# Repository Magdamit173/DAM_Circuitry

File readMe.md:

"DAM Circuitry" 
"Routing Stage"

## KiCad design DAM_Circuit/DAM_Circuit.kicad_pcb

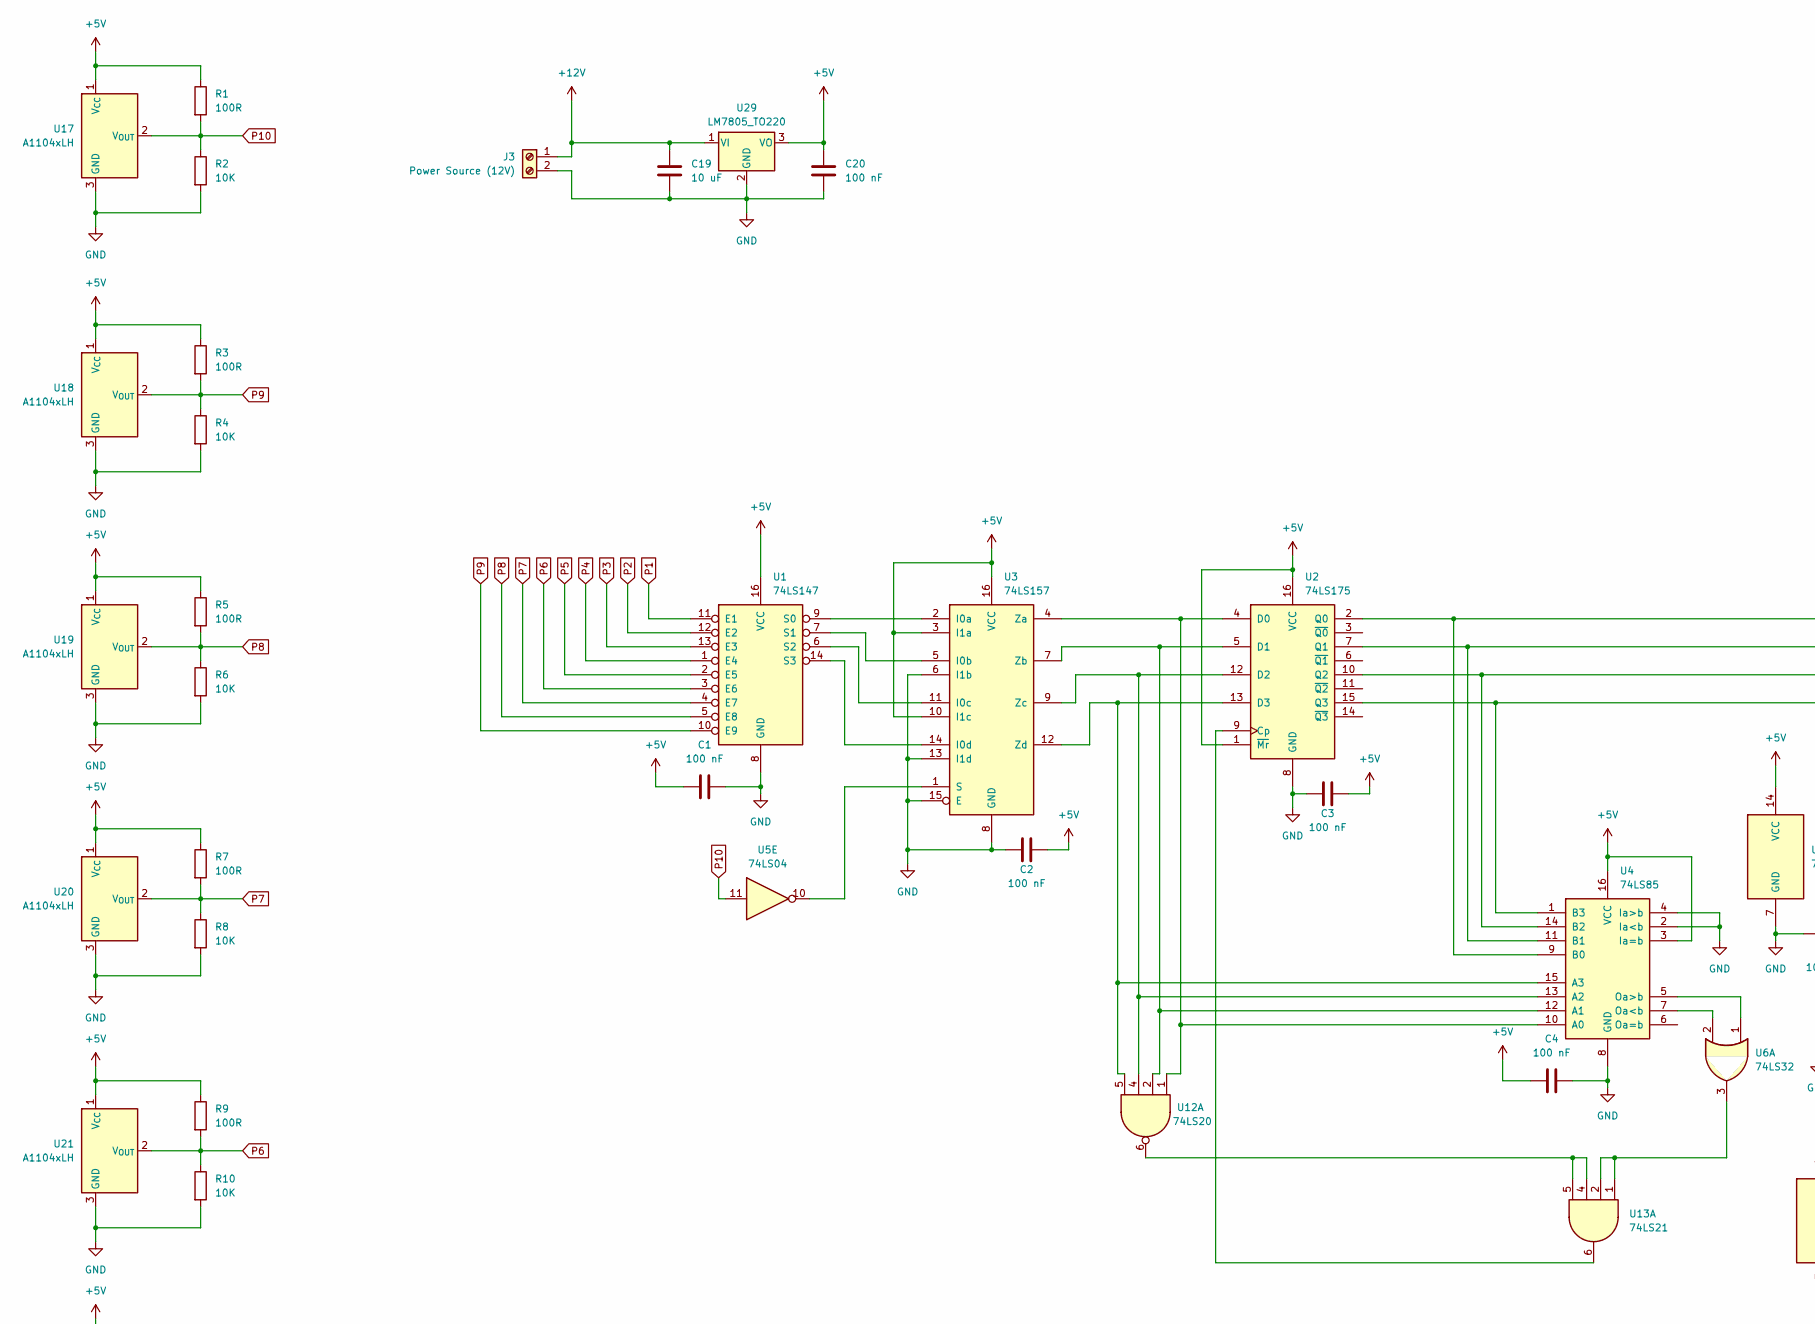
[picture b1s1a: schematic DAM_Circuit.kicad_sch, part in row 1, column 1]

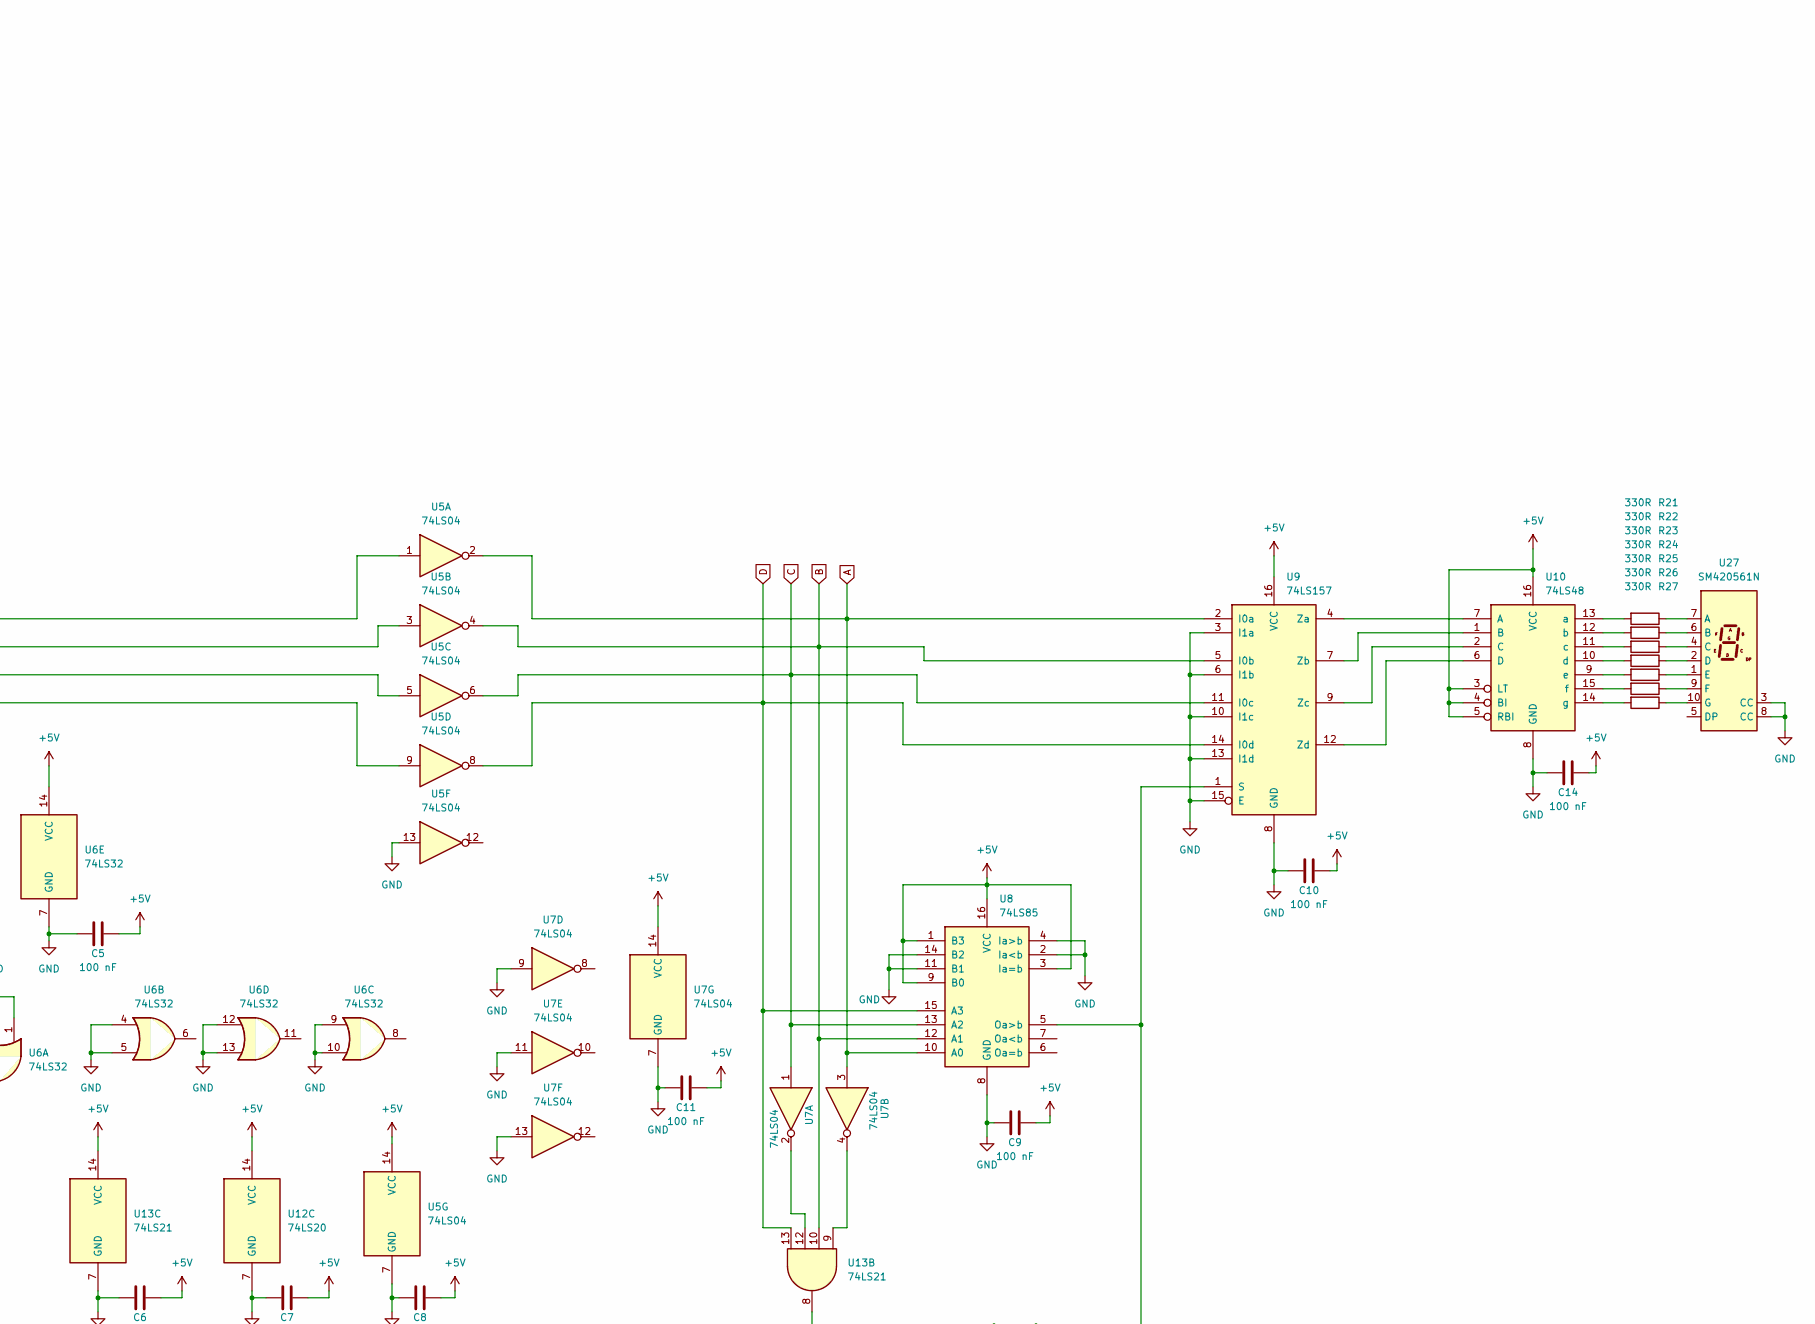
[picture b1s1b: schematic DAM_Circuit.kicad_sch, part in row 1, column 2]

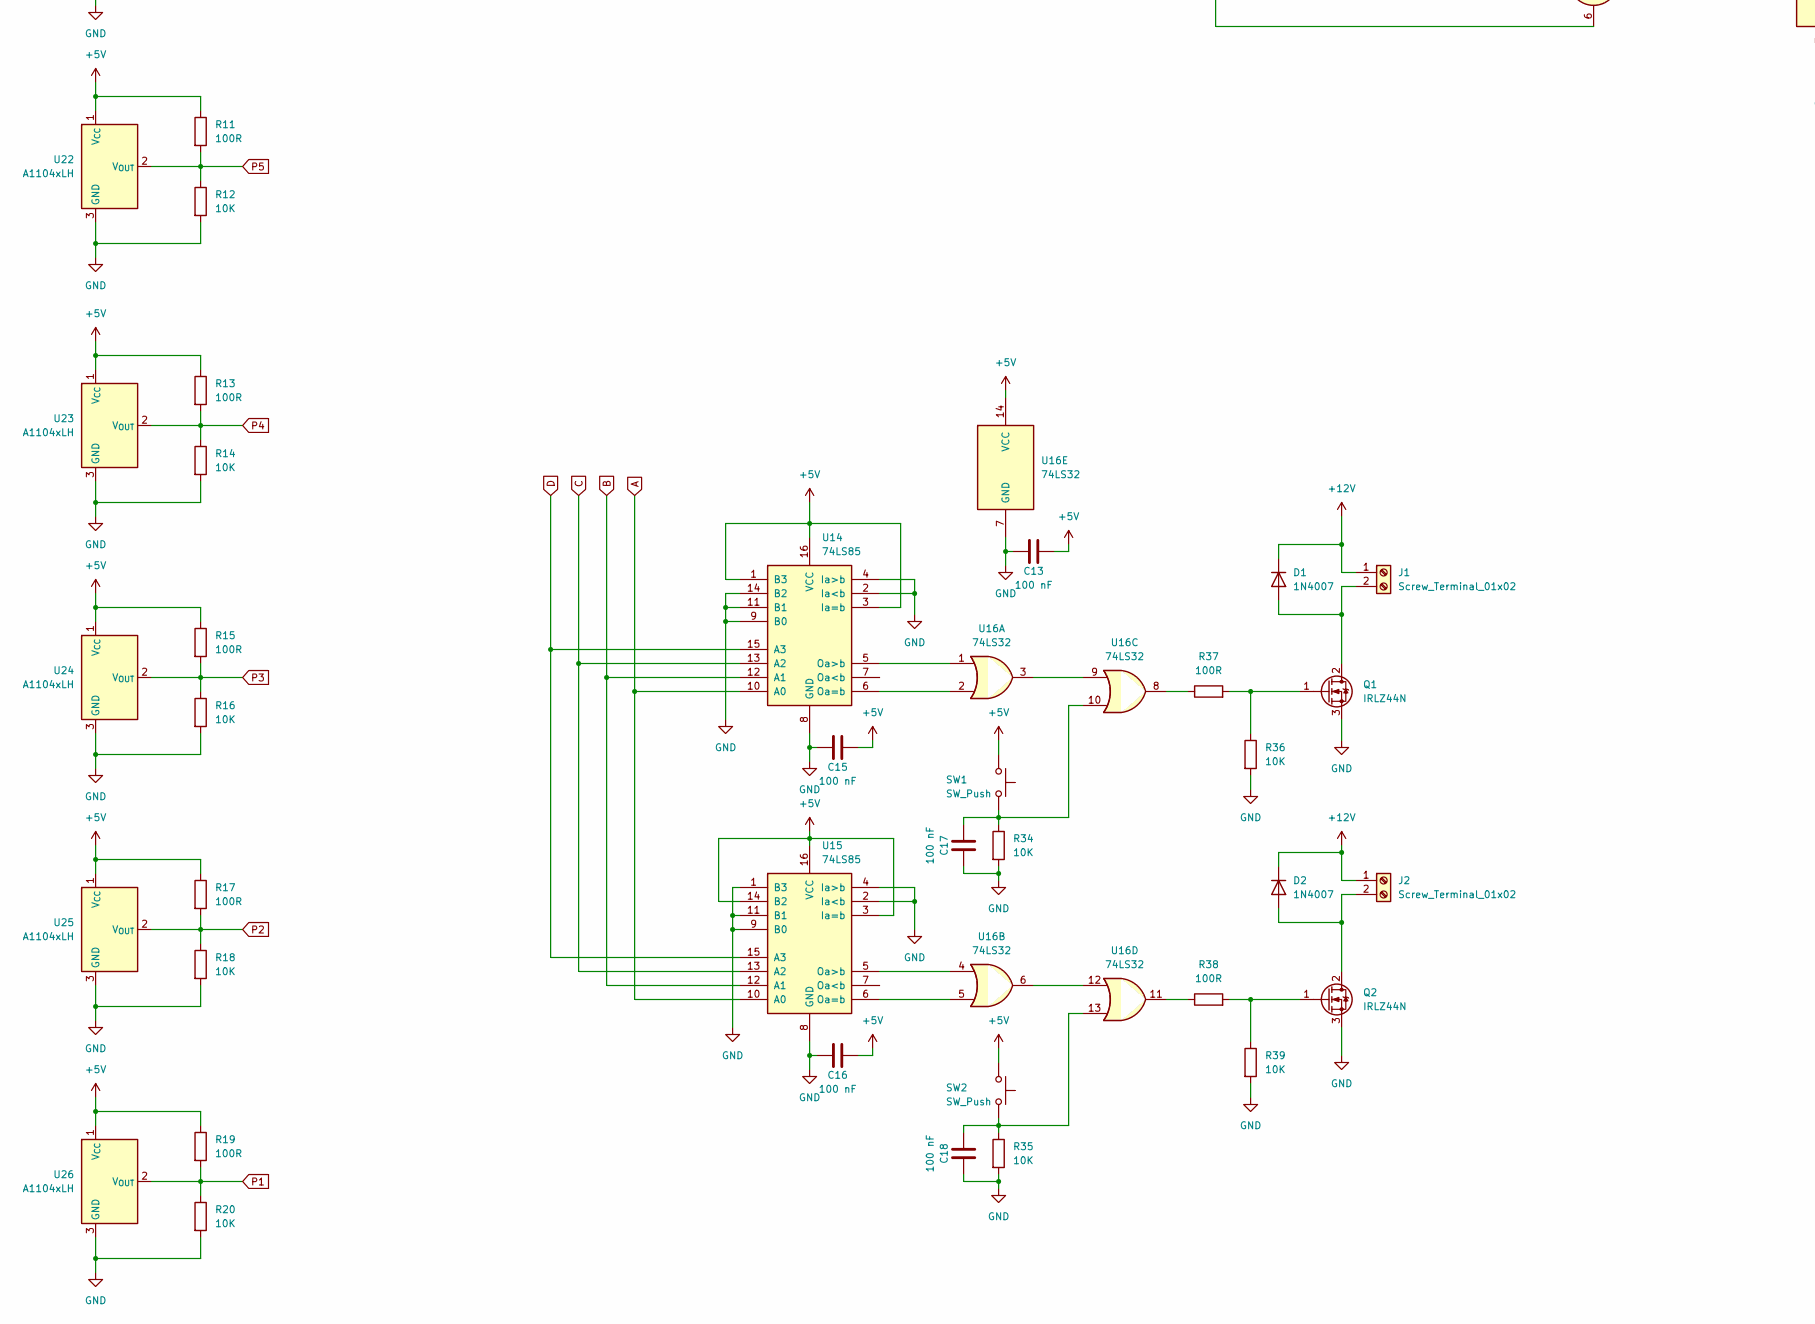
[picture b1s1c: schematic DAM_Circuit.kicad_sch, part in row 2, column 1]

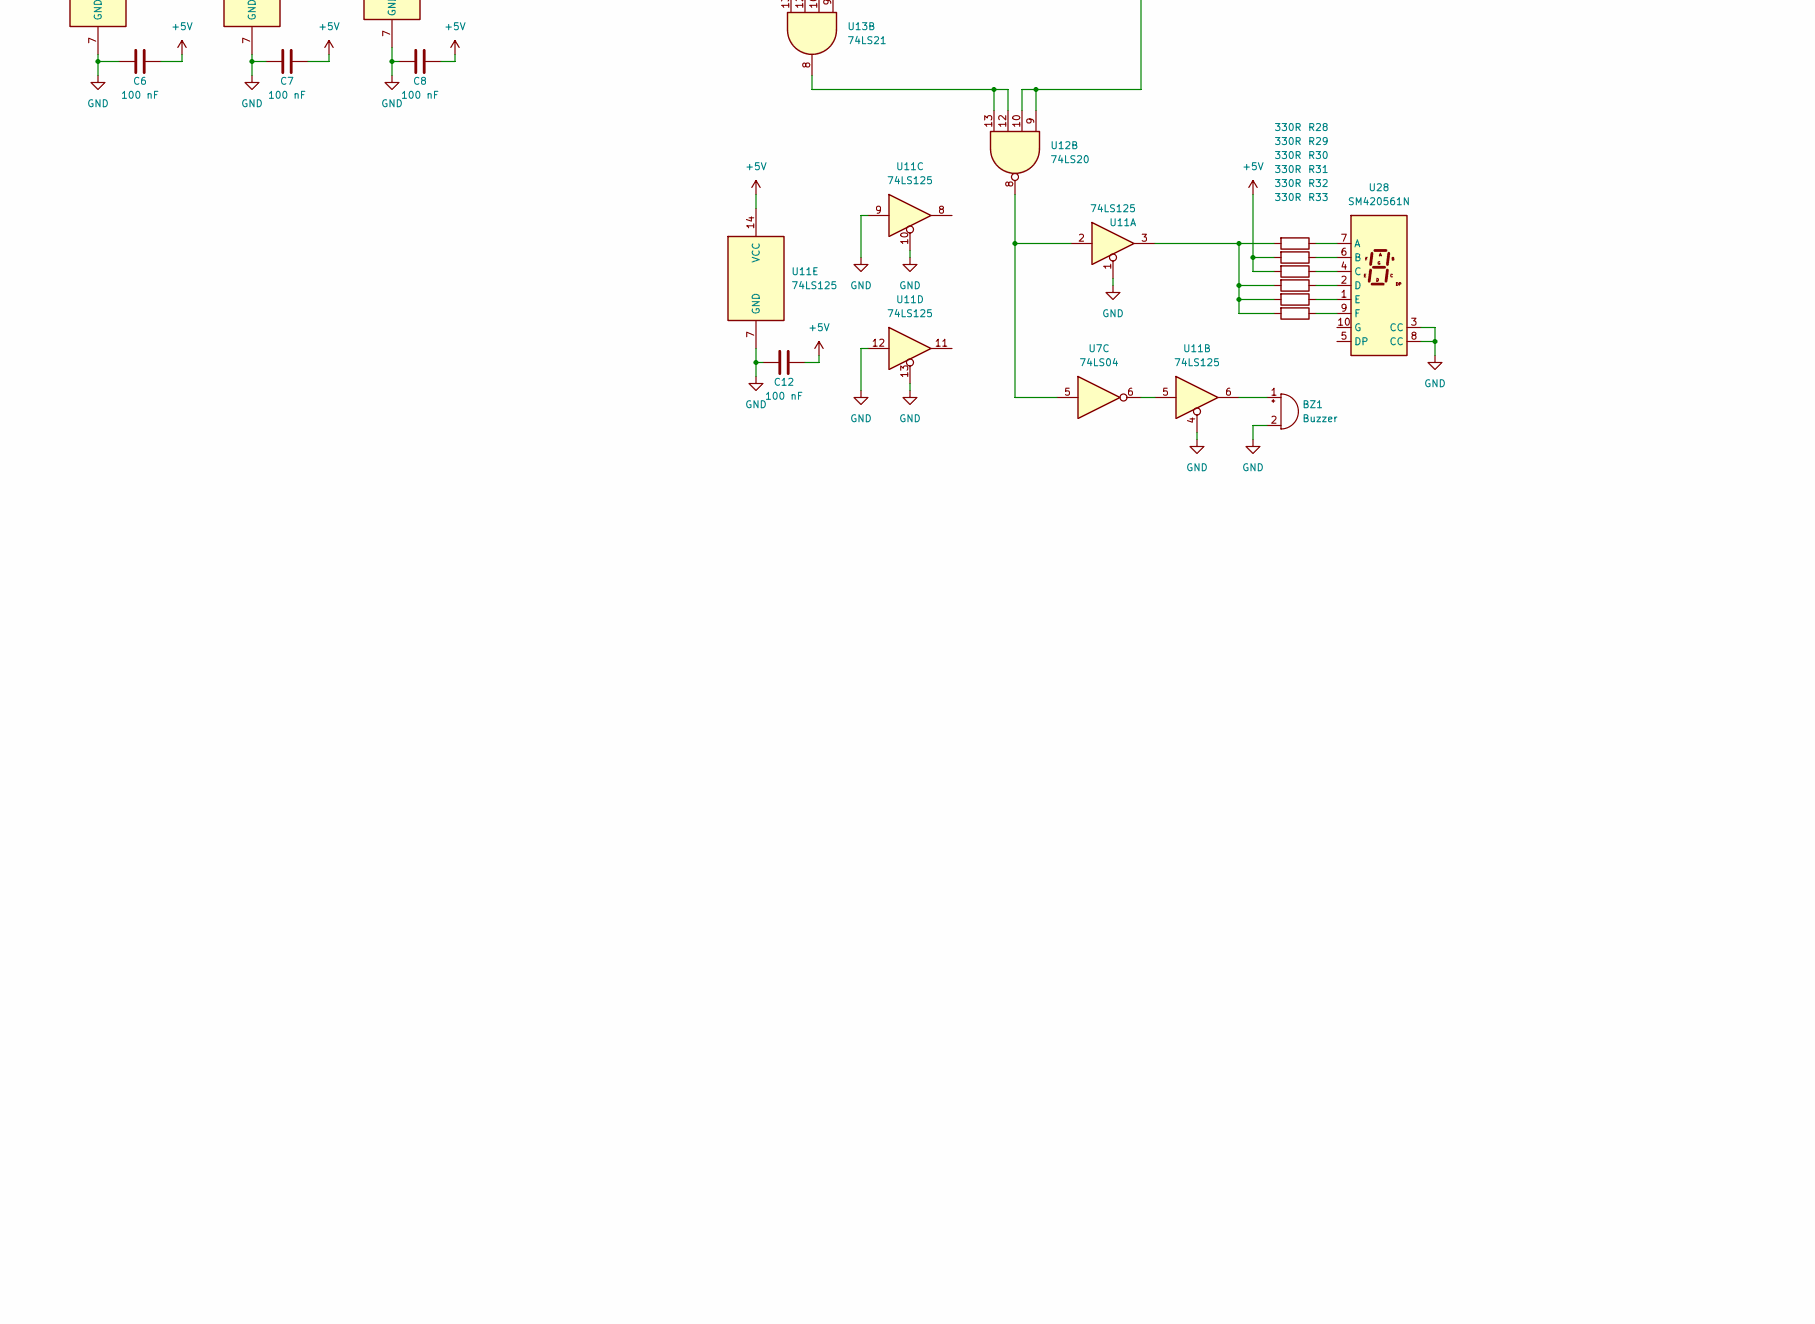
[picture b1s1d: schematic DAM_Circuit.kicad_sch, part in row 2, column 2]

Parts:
BZ1: Buzzer; TerminalBlock_Phoenix_MKDS-1,5-2_1x02_P5.00mm_Horizontal
C1, C2, C3, C4, C5, C6, C7, C8, C9, C10, C11, C12, C13, C14, C15, C16, C17, C18, C20: 100 nF; C_Disc_D5.0mm_W2.5mm_P5.00mm
C19: 10 uF; C_Disc_D5.0mm_W2.5mm_P5.00mm
D1, D2: 1N4007; D_DO-41_SOD81_P10.16mm_Horizontal
J1, J2: Screw_Terminal_01x02; TerminalBlock_Phoenix_MKDS-1,5-2_1x02_P5.00mm_Horizontal
J3: Power Source (12V); TerminalBlock_Phoenix_MKDS-1,5-2_1x02_P5.00mm_Horizontal
Q1, Q2: IRLZ44N; TO-220-3_Vertical
R1, R3, R5, R7, R9, R11, R13, R15, R17, R19, R37, R38: 100R; R_Axial_DIN0207_L6.3mm_D2.5mm_P10.16mm_Horizontal
R2, R4, R6, R8, R10, R12, R14, R16, R18, R20, R34, R35, R36, R39: 10K; R_Axial_DIN0207_L6.3mm_D2.5mm_P10.16mm_Horizontal
R21, R22, R23, R24, R25, R26, R27, R28, R29, R30, R31, R32, R33: 330R; R_Axial_DIN0207_L6.3mm_D2.5mm_P10.16mm_Horizontal
SW1, SW2: SW_Push; SW_PUSH_6mm_H5mm
U1: 74LS147; DIP-16_W7.62mm
U2: 74LS175; DIP-16_W7.62mm
U3, U9: 74LS157; DIP-16_W7.62mm
U4, U8, U14, U15: 74LS85; DIP-16_W7.62mm
U5, U7: 74LS04; DIP-14_W7.62mm
U6, U16: 74LS32; DIP-14_W7.62mm
U10: 74LS48; DIP-16_W7.62mm
U11: 74LS125; DIP-14_W7.62mm
U12: 74LS20; DIP-14_W7.62mm
U13: 74LS21; DIP-14_W7.62mm
U17, U18, U19, U20, U21, U22, U23, U24, U25, U26: A1104xLH; PinHeader_1x03_P2.54mm_Vertical
U27, U28: SM420561N; 7SegmentLED_LTS6760_LTS6780
U29: LM7805_TO220; TO-220-3_Vertical

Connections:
+5V: C1.1, C2.2, C3.2, C4.1, C5.2, C6.2, C7.2, C8.2, C9.2, C10.2, C11.2, C12.2, C13.2, C14.2, C15.2, C16.2, C20.2, R1.1, R3.1, R5.1, R7.1, R9.1, R11.1, R13.1, R15.1, R17.1, R19.1, R29.2, R30.2, SW1.1, SW2.1, U1.16 (VCC), U2.1 (~Mr), U2.16 (VCC), U3.3 (I1a), U3.10 (I1c), U3.16 (VCC), U4.3 (Ia=b), U4.16 (VCC), U5.14 (VCC), U6.14 (VCC), U7.14 (VCC), U8.1 (B3), U8.3 (Ia=b), U8.9 (B0), U8.16 (VCC), U9.16 (VCC), U10.3 (LT), U10.4 (BI), U10.5 (RBI), U10.16 (VCC), U11.14 (VCC), U12.14 (VCC), U13.14 (VCC), U14.1 (B3), U14.3 (Ia=b), U14.16 (VCC), U15.3 (Ia=b), U15.14 (B2), U15.16 (VCC), U16.14 (VCC), U17.1 (V_{CC}), U18.1 (V_{CC}), U19.1 (V_{CC}), U20.1 (V_{CC}), U21.1 (V_{CC}), U22.1 (V_{CC}), U23.1 (V_{CC}), U24.1 (V_{CC}), U25.1 (V_{CC}), U26.1 (V_{CC}), U29.3 (VO)
+12V: C19.2, D1.1 (K), D2.1 (K), J1.1, J2.1, J3.1, U29.1 (VI)
A: U5.2, U7.3, U8.10 (A0), U9.2 (I0a), U14.10 (A0), U15.10 (A0)
B: U5.4, U8.12 (A1), U9.5 (I0b), U13.10, U14.12 (A1), U15.12 (A1)
C: U5.6, U7.1, U8.13 (A2), U9.11 (I0c), U14.13 (A2), U15.13 (A2)
D: U5.8, U8.15 (A3), U9.14 (I0d), U13.13, U14.15 (A3), U15.15 (A3)
GND: BZ1.2 (-), C1.2, C2.1, C3.1, C4.2, C5.1, C6.1, C7.1, C8.1, C9.1, C10.1, C11.1, C12.1, C13.1, C14.1, C15.1, C16.1, C17.2, C18.2, C19.1, C20.1, J3.2, Q1.3 (S), Q2.3 (S), R2.2, R4.2, R6.2, R8.2, R10.2, R12.2, R14.2, R16.2, R18.2, R20.2, R34.2, R35.2, R36.2, R39.2, U1.8 (GND), U2.8 (GND), U3.6 (I1b), U3.8 (GND), U3.13 (I1d), U3.15 (E), U4.2 (Ia<b), U4.4 (Ia>b), U4.8 (GND), U5.7 (GND), U5.13, U6.4, U6.5, U6.7 (GND), U6.9, U6.10, U6.12, U6.13, U7.7 (GND), U7.9, U7.11, U7.13, U8.2 (Ia<b), U8.4 (Ia>b), U8.8 (GND), U8.11 (B1), U8.14 (B2), U9.3 (I1a), U9.6 (I1b), U9.8 (GND), U9.10 (I1c), U9.13 (I1d), U9.15 (E), U10.8 (GND), U11.1, U11.4, U11.7 (GND), U11.9, U11.10, U11.12, U11.13, U12.7 (GND), U13.7 (GND), U14.2 (Ia<b), U14.4 (Ia>b), U14.8 (GND), U14.9 (B0), U14.11 (B1), U14.14 (B2), U15.1 (B3), U15.2 (Ia<b), U15.4 (Ia>b), U15.8 (GND), U15.9 (B0), U15.11 (B1), U16.7 (GND), U17.3 (GND), U18.3 (GND), U19.3 (GND), U20.3 (GND), U21.3 (GND), U22.3 (GND), U23.3 (GND), U24.3 (GND), U25.3 (GND), U26.3 (GND), U27.3 (CC), U27.8 (CC), U28.3 (CC), U28.8 (CC), U29.2 (GND)
unnamed: BZ1.1 (+), U11.6
unnamed: C17.1, R34.1, SW1.2, U16.10
unnamed: C18.1, R35.1, SW2.2, U16.13
unnamed: D1.2 (A), J1.2, Q1.2 (D)
unnamed: D2.2 (A), J2.2, Q2.2 (D)
unnamed: Q1.1 (G), R36.1, R37.2
unnamed: Q2.1 (G), R38.2, R39.1
unnamed: R28.2, R31.2, R32.2, R33.2, U11.3
unnamed: R37.1, U16.8
unnamed: R38.1, U16.11
unnamed: U1.9 (S0), U3.2 (I0a)
unnamed: U1.7 (S1), U3.5 (I0b)
unnamed: U1.6 (S2), U3.11 (I0c)
unnamed: U1.14 (S3), U3.14 (I0d)
unnamed: U2.9 (Cp), U13.6
unnamed: U2.4 (D0), U3.4 (Za), U4.10 (A0), U12.1
unnamed: U2.5 (D1), U3.7 (Zb), U4.12 (A1), U12.2
unnamed: U2.12 (D2), U3.9 (Zc), U4.13 (A2), U12.4
unnamed: U2.13 (D3), U3.12 (Zd), U4.15 (A3), U12.5
unnamed: U2.2 (Q0), U4.9 (B0), U5.1
unnamed: U2.7 (Q1), U4.11 (B1), U5.3
unnamed: U2.10 (Q2), U4.14 (B2), U5.5
unnamed: U2.15 (Q3), U4.1 (B3), U5.9
unnamed: U3.1 (S), U5.10
unnamed: U4.7 (Oa<b), U6.2
unnamed: U4.5 (Oa>b), U6.1
unnamed: U8.5 (Oa>b), U9.1 (S), U12.9, U12.10
unnamed: U9.4 (Za), U10.7 (A)
unnamed: U9.7 (Zb), U10.1 (B)
unnamed: U9.9 (Zc), U10.2 (C)
unnamed: U9.12 (Zd), U10.6 (D)
unnamed: R21.2, U10.13 (a)
unnamed: R22.2, U10.12 (b)
unnamed: R23.2, U10.11 (c)
unnamed: R24.2, U10.10 (d)
unnamed: R25.2, U10.9 (e)
unnamed: R26.2, U10.15 (f)
unnamed: R27.2, U10.14 (g)
unnamed: U7.5, U11.2, U12.8
unnamed: U7.6, U11.5
unnamed: U12.6, U13.4, U13.5
unnamed: U12.12, U12.13, U13.8
unnamed: U6.3, U13.1, U13.2
unnamed: U7.4, U13.9
unnamed: U7.2, U13.12
unnamed: U14.6 (Oa=b), U16.2
unnamed: U14.5 (Oa>b), U16.1
unnamed: U15.6 (Oa=b), U16.5
unnamed: U15.5 (Oa>b), U16.4
unnamed: U16.3, U16.9
unnamed: U16.6, U16.12
unnamed: R21.1, U27.7 (A)
unnamed: R22.1, U27.6 (B)
unnamed: R23.1, U27.4 (C)
unnamed: R24.1, U27.2 (D)
unnamed: R25.1, U27.1 (E)
unnamed: R26.1, U27.9 (F)
unnamed: R27.1, U27.10 (G)
unnamed: R28.1, U28.7 (A)
unnamed: R29.1, U28.6 (B)
unnamed: R30.1, U28.4 (C)
unnamed: R31.1, U28.2 (D)
unnamed: R32.1, U28.1 (E)
unnamed: R33.1, U28.9 (F)
P1: R19.2, R20.1, U1.11 (E1), U26.2 (V_{OUT})
P2: R17.2, R18.1, U1.12 (E2), U25.2 (V_{OUT})
P3: R15.2, R16.1, U1.13 (E3), U24.2 (V_{OUT})
P4: R13.2, R14.1, U1.1 (E4), U23.2 (V_{OUT})
P5: R11.2, R12.1, U1.2 (E5), U22.2 (V_{OUT})
P6: R9.2, R10.1, U1.3 (E6), U21.2 (V_{OUT})
P7: R7.2, R8.1, U1.4 (E7), U20.2 (V_{OUT})
P8: R5.2, R6.1, U1.5 (E8), U19.2 (V_{OUT})
P9: R3.2, R4.1, U1.10 (E9), U18.2 (V_{OUT})
P10: R1.2, R2.1, U5.11, U17.2 (V_{OUT})

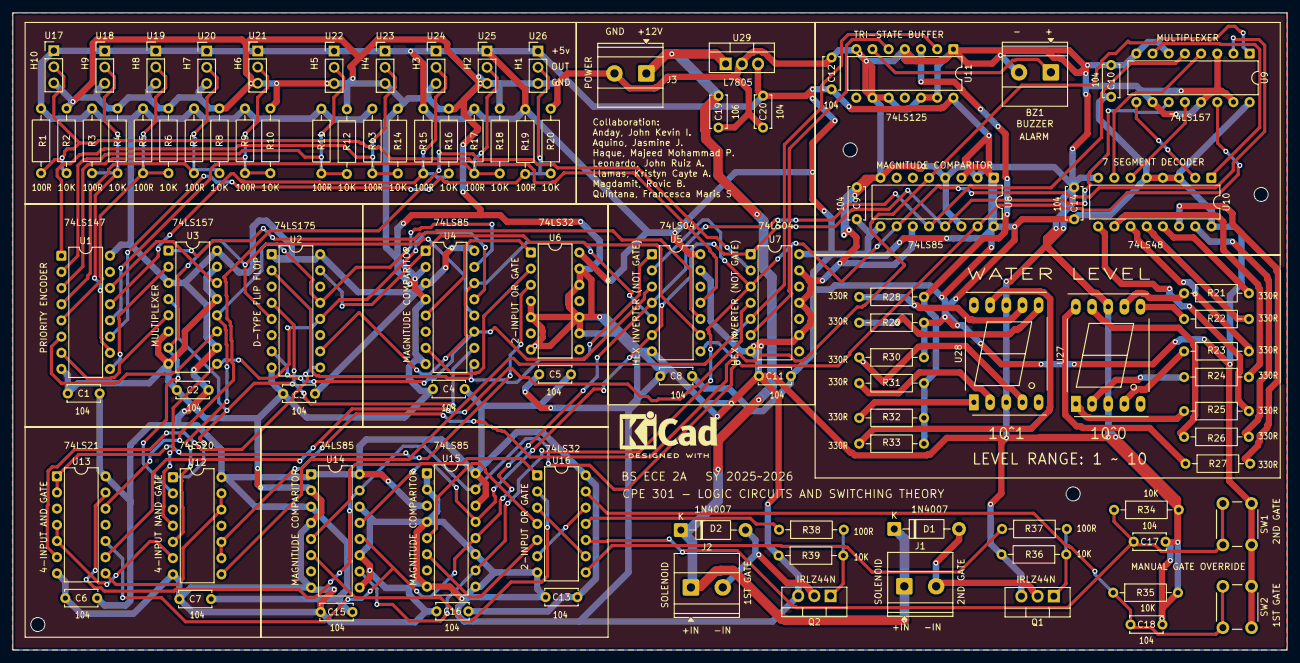
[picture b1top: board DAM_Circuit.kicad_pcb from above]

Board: 2 copper layers, 200.0 x 100.0 mm, 98 parts (0 on the bottom side), 81 nets.

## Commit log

2026-06-02 6.3.2026
2026-06-05 6.6.2026 --added multiple version of the circuit update
2026-06-06 6.6.2026 --cleaned
2026-06-06 6.6.2026 --updated pcb
2026-06-06 6.6.2026 finalized schematic
2026-06-06 6.7.2026 layout but no routing
2026-06-06 6.7.2026 time=3:33 finalized schematic position please route manually
2026-06-07 6.7.2026 already routed, need to compress more
2026-06-07 6.7.2026 zoning is done, added drill holes, added grouping only last thing is gerber files
2026-06-07 6.7.2026 v1 gerber added, complete
